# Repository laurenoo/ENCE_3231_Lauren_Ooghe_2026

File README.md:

# ENCE_3231_Lauren_Ooghe_2026
I did not complete this lab, but I tried using Timer 2 to create the 10us pulse. I used a prescalar of 83 and counter period of 9 to produce a 0.00001 s pulse. The block diagram was incomplete as well.

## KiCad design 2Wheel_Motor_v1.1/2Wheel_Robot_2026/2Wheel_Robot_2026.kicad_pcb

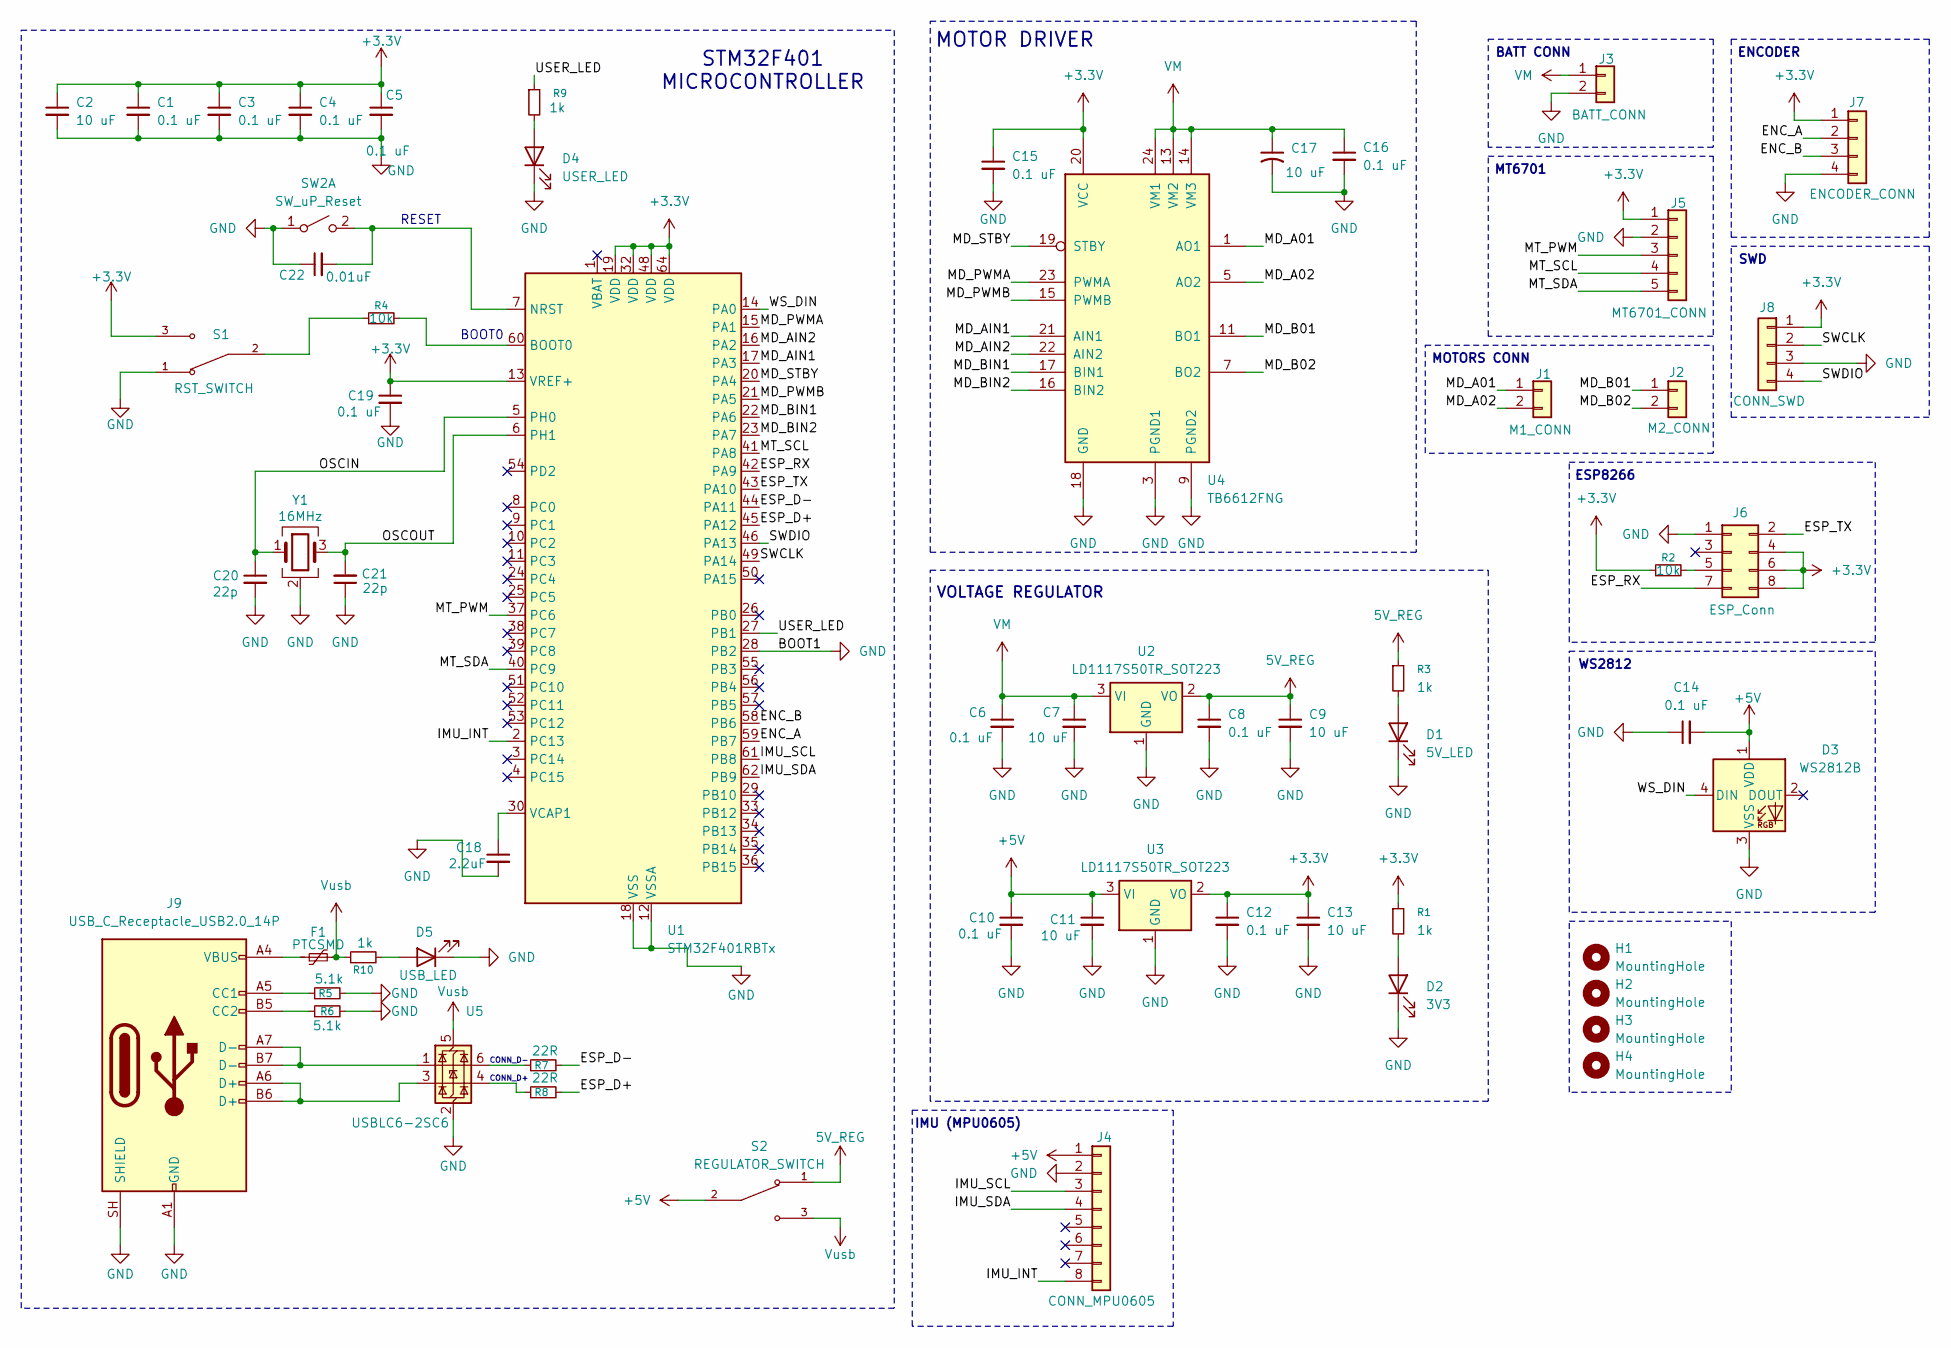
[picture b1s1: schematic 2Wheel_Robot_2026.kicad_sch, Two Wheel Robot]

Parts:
C1, C3, C4, C5, C6, C8, C10, C12, C14, C15, C16, C19: 0.1 uF; C_0805_2012Metric_Pad1.18x1.45mm_HandSolder; MFR# KAM21BR71H104JM
C2, C7, C9, C11, C13: 10 uF; C_0805_2012Metric_Pad1.18x1.45mm_HandSolder; MFR# KAM21BR71H104JM
C17: 10 uF; C_0805_2012Metric_Pad1.18x1.45mm_HandSolder
C18: 2.2uF; C_0805_2012Metric_Pad1.18x1.45mm_HandSolder; MFR# KAM21BR71H104JM
C20, C21: 22p; C_0805_2012Metric_Pad1.18x1.45mm_HandSolder; MFR# KAM21BR71H104JM
C22: 0.01uF; C_0805_2012Metric_Pad1.18x1.45mm_HandSolder; MFR# KAM21BR71H104JM
D1: 5V_LED; LED_0805_2012Metric_Pad1.15x1.40mm_HandSolder
D2: 3V3; LED_0805_2012Metric_Pad1.15x1.40mm_HandSolder
D3: WS2812B; LED_WS2812B_PLCC4_5.0x5.0mm_P3.2mm
D4: USER_LED; LED_0805_2012Metric_Pad1.15x1.40mm_HandSolder
D5: USB_LED; LED_0805_2012Metric_Pad1.15x1.40mm_HandSolder
F1: PTCSMD; Fuse_1812_4532Metric
H1, H2, H3, H4: MountingHole; MountingHole_2.2mm_M2
J1: M1_CONN; JST_XH_B2B-XH-A_1x02_P2.50mm_Vertical
J2: M2_CONN; JST_XH_B2B-XH-A_1x02_P2.50mm_Vertical
J3: BATT_CONN; JST_XH_B2B-XH-A_1x02_P2.50mm_Vertical
J4: CONN_MPU0605; PinSocket_1x08_P2.54mm_Vertical
J5: MT6701_CONN; JST_XH_B5B-XH-A_1x05_P2.50mm_Vertical
J6: ESP_Conn; PinSocket_2x04_P2.54mm_Vertical
J7: ENCODER_CONN; JST_XH_B4B-XH-A_1x04_P2.50mm_Vertical
J8: CONN_SWD; PinHeader_1x04_P2.54mm_Vertical
J9: USB_C_Receptacle_USB2.0_14P; USB_C_Receptacle_HCTL_HC-TYPE-C-16P-01A
R1, R3, R9, R10: 1k; R_0805_2012Metric_Pad1.20x1.40mm_HandSolder
R2, R4: 10k; R_0805_2012Metric_Pad1.20x1.40mm_HandSolder
R5, R6: 5.1k; R_0805_2012Metric_Pad1.20x1.40mm_HandSolder
R7, R8: 22R; R_0805_2012Metric_Pad1.20x1.40mm_HandSolder
S1: RST_SWITCH; SW_SLW-66527511-SMT-TR; PARTREV 1.01
S2: REGULATOR_SWITCH; SW_SLW-66527511-SMT-TR; PARTREV 1.01
SW2: SW_uP_Reset
U1: STM32F401RBTx; LQFP-64_10x10mm_P0.5mm; MFR# STM32F401RET6
U2, U3: LD1117S50TR_SOT223; SOT-223-3_TabPin2
U4: TB6612FNG; SSOP-24_5.3x8.2mm_P0.65mm
U5: USBLC6-2SC6; SOT-23-6
Y1: 16MHz; Crystal_SMD_Abracon_ABM8G-4Pin_3.2x2.5mm

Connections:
5V_REG: C8.1, C9.1, R3.1, S2.1, U2.2 (VO)
+3.3V: C1.1, C2.1, C3.1, C4.1, C5.1, C12.1, C13.1, C15.1, C19.1, J5.1, J6.4, J6.6, J6.8, J7.1, J8.1, R1.1, R2.1, S1.3, U1.13 (VREF+), U1.19 (VDD), U1.32 (VDD), U1.48 (VDD), U1.64 (VDD), U3.2 (VO), U4.20 (VCC)
+5V: C10.1, C11.1, C14.2, D3.1 (VDD), J4.1, S2.2, U3.3 (VI)
/ENC_A: J7.2, U1.59 (PB7)
/ENC_B: J7.3, U1.58 (PB6)
/ESP_D+: R8.2, U1.45 (PA12)
/ESP_D-: R7.2, U1.44 (PA11)
/ESP_RX: J6.7, U1.42 (PA9)
/ESP_TX: J6.2, U1.43 (PA10)
/IMU_INT: J4.8, U1.2 (PC13)
/IMU_SCL: J4.3, U1.61 (PB8)
/IMU_SDA: J4.4, U1.62 (PB9)
/MD_A01: J1.1, U4.1 (AO1), U4.2 (AO1)
/MD_A02: J1.2, U4.5 (AO2), U4.6 (AO2)
/MD_AIN1: U1.17 (PA3), U4.21 (AIN1)
/MD_AIN2: U1.16 (PA2), U4.22 (AIN2)
/MD_B01: J2.1, U4.11 (BO1), U4.12 (BO1)
/MD_B02: J2.2, U4.7 (BO2), U4.8 (BO2)
/MD_BIN1: U1.22 (PA6), U4.17 (BIN1)
/MD_BIN2: U1.23 (PA7), U4.16 (BIN2)
/MD_PWMA: U1.15 (PA1), U4.23 (PWMA)
/MD_PWMB: U1.21 (PA5), U4.15 (PWMB)
/MD_STBY: U1.20 (PA4), U4.19 (STBY)
/MT_PWM: J5.3, U1.37 (PC6)
/MT_SCL: J5.4, U1.41 (PA8)
/MT_SDA: J5.5, U1.40 (PC9)
/OSCIN: C20.1, U1.5 (PH0), Y1.1
/OSCOUT: C21.2, U1.6 (PH1), Y1.3
/SWCLK: J8.2, U1.49 (PA14)
/SWDIO: J8.4, U1.46 (PA13)
/USER_LED: R9.1, U1.27 (PB1)
/WS_DIN: D3.4 (DIN), U1.14 (PA0)
GND: C1.2, C2.2, C3.2, C4.2, C5.2, C6.2, C7.2, C8.2, C9.2, C10.2, C11.2, C12.2, C13.2, C14.1, C15.2, C16.2, C17.2, C18.2, C19.2, C20.2, C21.1, C22.1, D1.1 (K), D2.1 (K), D3.3 (VSS), D4.1 (K), D5.1 (K), J3.2, J4.2, J5.2, J6.1, J7.4, J8.3, J9.A1 (GND), J9.A12 (GND), J9.B1 (GND), J9.B12 (GND), J9.SH (SHIELD), R5.2, R6.2, S1.1, SW2.1 (A), U1.12 (VSSA), U1.18 (VSS), U1.28 (PB2), U1.31 (VSS), U1.47 (VSS), U1.63 (VSS), U2.1 (GND), U3.1 (GND), U4.3 (PGND1), U4.4 (PGND1), U4.9 (PGND2), U4.10 (PGND2), U4.18 (GND), U5.2 (GND), Y1.2 (G), Y1.4 (G)
unnamed: D1.2 (A), R3.2
unnamed: D2.2 (A), R1.2
unnamed: D4.2 (A), R9.2
unnamed: D5.2 (A), R10.2
unnamed: F1.1, J9.A4 (VBUS), J9.A9 (VBUS), J9.B4 (VBUS), J9.B9 (VBUS)
unnamed: J6.5, R2.2
unnamed: J9.A5 (CC1), R5.1
unnamed: J9.B5 (CC2), R6.1
unnamed: J9.A6 (D+), J9.B6 (D+), U5.3 (I/O2)
unnamed: J9.A7 (D-), J9.B7 (D-), U5.1 (I/O1)
unnamed: R4.1, S1.2
unnamed: R7.1, U5.6 (I/O1)
unnamed: R8.1, U5.4 (I/O2)
unnamed: C22.2, SW2.2 (B), U1.7 (NRST)
unnamed: R4.2, U1.60 (BOOT0)
unnamed: C18.1, U1.30 (VCAP1)
VM: C6.1, C7.1, C16.1, C17.1, J3.1, U2.3 (VI), U4.13 (VM2), U4.14 (VM3), U4.24 (VM1)
Vusb: F1.2, R10.1, S2.3, U5.5 (VBUS)

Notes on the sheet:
CONN_D-
MOTOR DRIVER
STM32F401 MICROCONTROLLER
VOLTAGE REGULATOR
MT6701
ENCODER
MOTORS CONN
BATT CONN
BOOT0
ESP8266
SWD
RESET
CONN_D+
IMU (MPU0605)
WS2812

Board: 2 copper layers, 60 parts (0 on the bottom side), 51 nets, no tracks yet.

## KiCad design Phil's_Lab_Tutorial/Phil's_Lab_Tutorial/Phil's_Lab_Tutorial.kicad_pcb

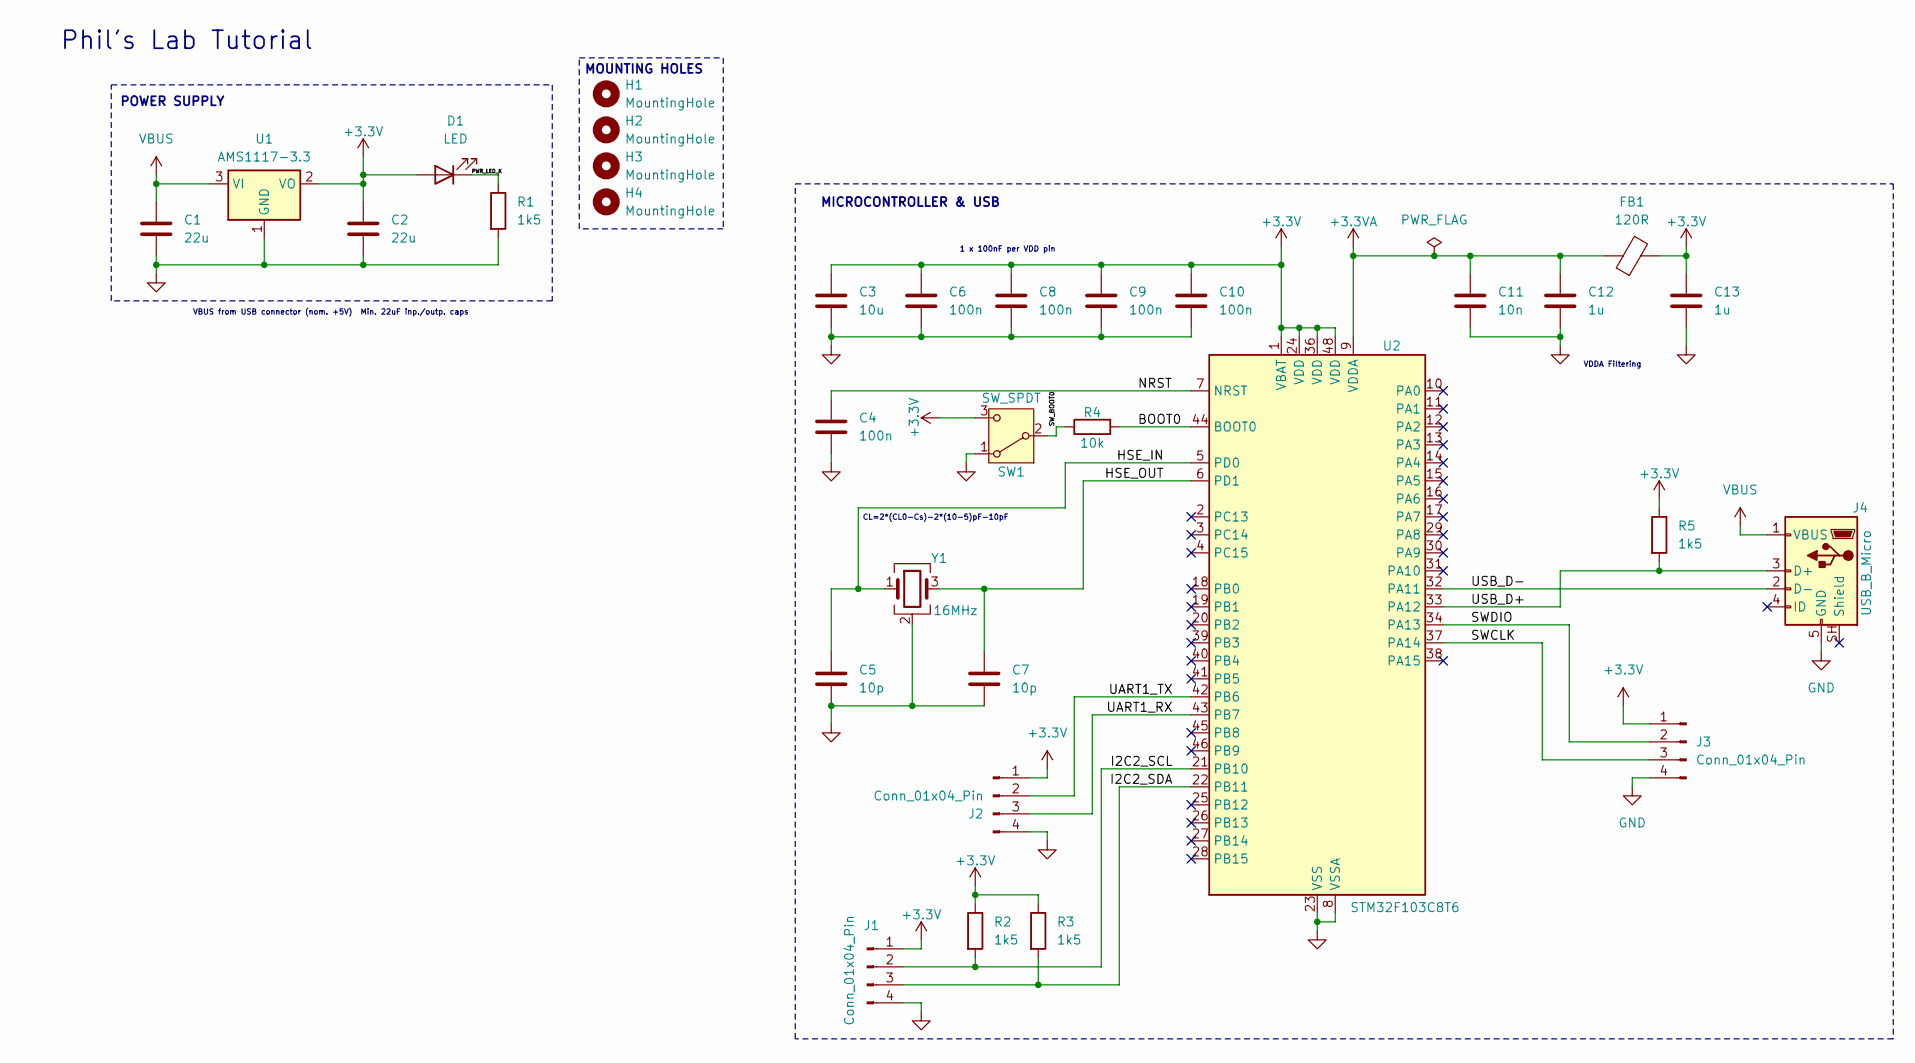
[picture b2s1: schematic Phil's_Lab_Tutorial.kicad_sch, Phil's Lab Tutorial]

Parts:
C1, C2: 22u; C_0805_2012Metric
C3: 10u; C_0603_1608Metric
C4, C6, C8, C9, C10: 100n; C_0402_1005Metric
C5, C7: 10p; C_0402_1005Metric
C11: 10n; C_0402_1005Metric
C12, C13: 1u; C_0402_1005Metric
D1: LED; LED_0805_2012Metric
FB1: 120R; L_0603_1608Metric
H1, H2, H3, H4: MountingHole; MountingHole_2.2mm_M2
J1, J2, J3: Conn_01x04_Pin; PinHeader_1x04_P2.54mm_Vertical
J4: USB_B_Micro; USB_Micro-B_Wuerth_629105150521
R1, R2, R3, R5: 1k5; R_0402_1005Metric
R4: 10k; R_0402_1005Metric
SW1: SW_SPDT; SW_SPDT_PCM12
U1: AMS1117-3.3; SOT-223-3_TabPin2
U2: STM32F103C8T6; LQFP-48_7x7mm_P0.5mm
Y1: 16MHz; Crystal_SMD_3225-4Pin_3.2x2.5mm

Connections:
+3.3V: C2.1, C3.1, C6.1, C8.1, C9.1, C10.1, C13.1, D1.2 (A), FB1.2, J1.1, J2.1, J3.1, R2.1, R3.1, R5.1, SW1.3 (C), U1.2 (VO), U2.1 (VBAT), U2.24 (VDD), U2.36 (VDD), U2.48 (VDD)
+3.3VA: C11.1, C12.1, FB1.1, U2.9 (VDDA)
/BOOT0: R4.2, U2.44 (BOOT0)
/HSE_IN: C5.1, U2.5 (PD0), Y1.1
/HSE_OUT: C7.1, U2.6 (PD1), Y1.3
/I2C2_SCL: J1.2, R2.2, U2.21 (PB10)
/I2C2_SDA: J1.3, R3.2, U2.22 (PB11)
/NRST: C4.1, U2.7 (NRST)
/PWR_LED_K: D1.1 (K), R1.1
/SWCLK: J3.3, U2.37 (PA14)
/SWDIO: J3.2, U2.34 (PA13)
/SW_BOOT0: R4.1, SW1.2 (B)
/UART1_RX: J2.3, U2.43 (PB7)
/UART1_TX: J2.2, U2.42 (PB6)
/USB_D+: J4.3 (D+), R5.2, U2.33 (PA12)
/USB_D-: J4.2 (D-), U2.32 (PA11)
GND: C1.2, C2.2, C3.2, C4.2, C5.2, C6.2, C7.2, C8.2, C9.2, C10.2, C11.2, C12.2, C13.2, J1.4, J2.4, J3.4, J4.5 (GND), R1.2, SW1.1 (A), U1.1 (GND), U2.8 (VSSA), U2.23 (VSS), U2.35 (VSS), U2.47 (VSS), Y1.2 (G), Y1.4 (G)
VBUS: C1.1, J4.1 (VBUS), U1.3 (VI)

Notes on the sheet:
VBUS from USB connector (nom. +5V) Min. 22uF inp./outp. caps
MICROCONTROLLER & USB
1 x 100nF per VDD pin
Phil's Lab Tutorial
MOUNTING HOLES
POWER SUPPLY
CL=2*(CL0-Cs)-2*(10-5)pF-10pF
VDDA Filtering

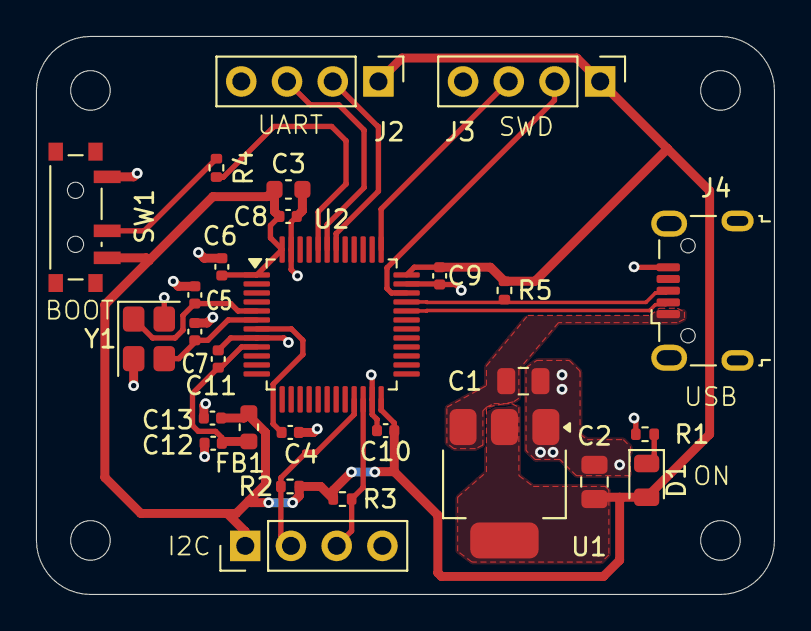
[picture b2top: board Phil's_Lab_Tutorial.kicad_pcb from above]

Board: 2 copper layers, 41.0 x 31.0 mm, 32 parts (0 on the bottom side), 18 nets.

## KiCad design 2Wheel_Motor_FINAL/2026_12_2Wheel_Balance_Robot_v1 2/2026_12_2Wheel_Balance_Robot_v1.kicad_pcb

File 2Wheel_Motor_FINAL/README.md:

# 2-Wheel Robot Design
## This project incorporates the use of program and design software such as STMCubeIDE and KiCad.
## Introduction
The main objective was to design and create a two-wheeled balancing robot using an STM32F401 microcontroller. All components were assembled to include soldering all components on the fabricated PCB, designing and cutting the acrylic chassis, and implementing test code for a 3-wheeled function to use for threshold testing.

### Block Diagram and System Diagram

 ### Design
 The PCB was designed in KiCAD and the images of layout and schematics can be seen below.

### Prototyping
Once all components were verified working, such as the ESP8266 wifi chip, the motors, and the USB connection, the chassis was designed using OnShape CAD program to provide a drawing that could be used to verify part placement such as the PCB, motor mounts, battery pack, and front caster wheel. 

Once the layout was verified with a 'dry fit', a .DXF file was downloaded from the CAD software and used in the laser cutter to shape and cut the acrylic chassis. All components were mounted and the robot was ready for testing.

### Testing
The 3-Wheel system is controlled by the use of an ESP8266 that provides a wifi signal (Access Point) to connect to a phone or tablet. The IP address is typed into the device and interfaces with the robot to perform manuevers such as forward, backward, left, right, or stop. The remote also receives a stream of data that is updated every 100 ms such as pitch, roll, velocity, and a counter. 

https://github.com/user-attachments/assets/3100aa6c-19b2-47c0-a776-326ca26b746c

Once the 3-wheeled task was completed, I was motivated to try to incorporate PID control to balance on two wheels. This introduced the encoder which was orignally to be an MT6701 but we were provided with an AS5600. The difference between these components is the address it uses to connect through I2C. I used Claude code to create a ".h" and ".c" file to include in the "main.c" program to initiate the encoder. Once this was accomplished, the code was written, tested, and verified. The testing consisted of finding the natural pitch recorded when the robot is balanced. This was used as the setpoint needed to determine whether the robot needs to correct forward or backward. Ultimately, the 2-wheel balanced was acheived but not perfected. 

https://github.com/user-attachments/assets/a37571b3-f4c5-43bc-a98e-a4f5ce808e1f

#### *** All PCB design materials and images are located in folder 2026_12_2Wheel_Balance_Robot_v1 2 ***
PCB layout used from Dr. Martins provided layout

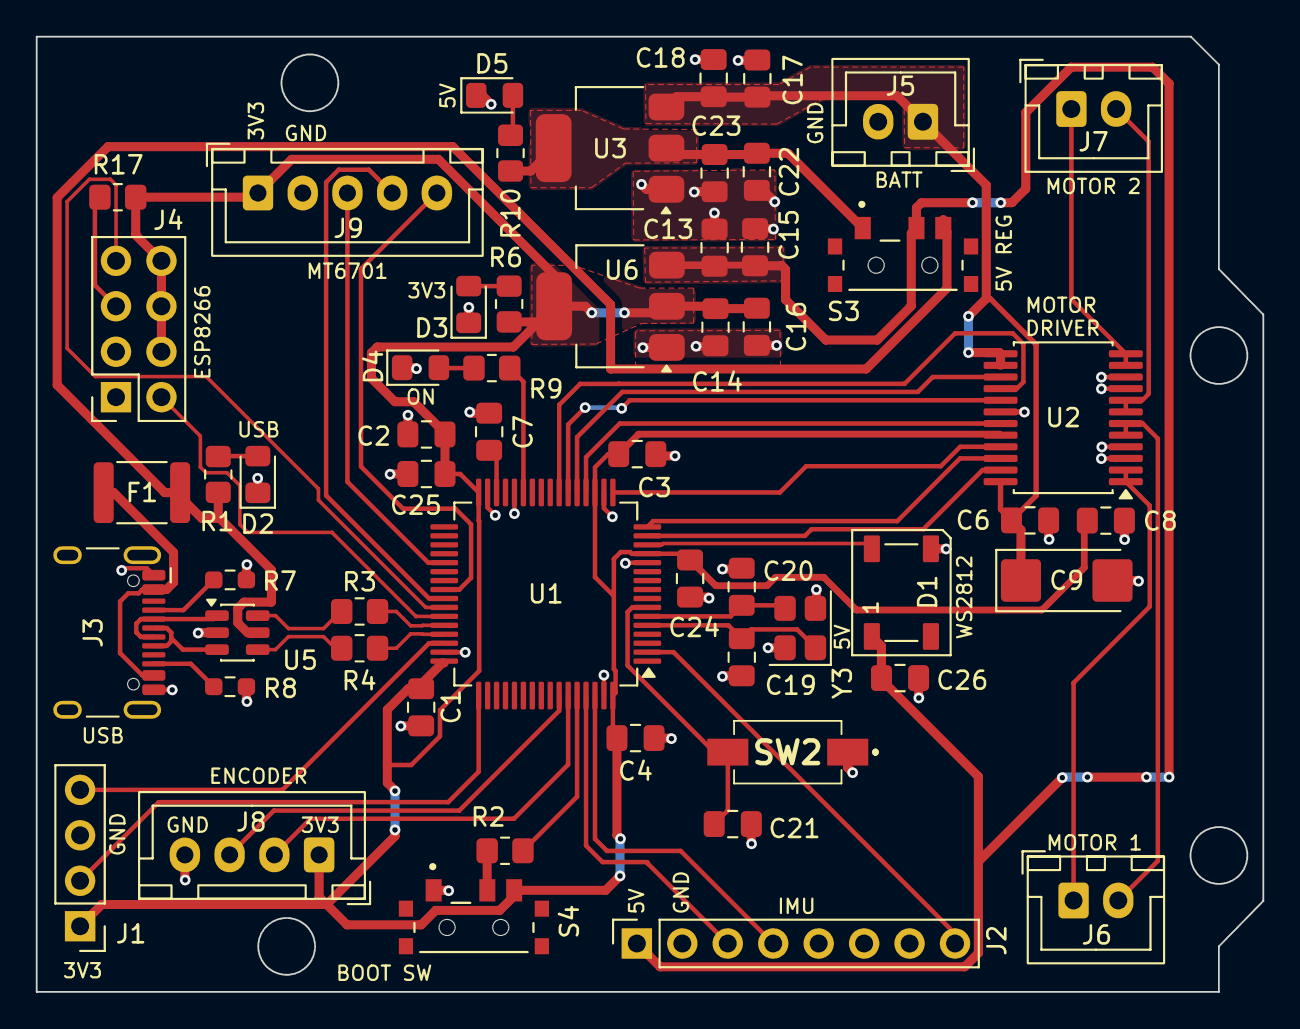
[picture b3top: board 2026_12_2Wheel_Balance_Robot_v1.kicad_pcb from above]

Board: 2 copper layers, 68.6 x 53.4 mm, 57 parts (1 on the bottom side), 51 nets.

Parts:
C1, C2, C3, C4, C6, C8, C13, C14, C17, C22, C24, C26: 0.1uF; C_0805_2012Metric_Pad1.18x1.45mm_HandSolder
C7: 2.2uF; C_0805_2012Metric_Pad1.18x1.45mm_HandSolder
C9: 10uF; CP_EIA-6032-28_Kemet-C_HandSolder
C15, C16, C18, C23, C25: 10uF; C_0805_2012Metric_Pad1.18x1.45mm_HandSolder
C19, C20: 22p; C_0805_2012Metric_Pad1.18x1.45mm_HandSolder
C21: 0.01uF; C_0805_2012Metric_Pad1.18x1.45mm_HandSolder
D1: WS2812B; LED_WS2812B_PLCC4_5.0x5.0mm_P3.2mm
D2: USB_LED; LED_0805_2012Metric_Pad1.15x1.40mm_HandSolder
D3: 3V3_LED; LED_0805_2012Metric_Pad1.15x1.40mm_HandSolder
D4: USER_LED; LED_0805_2012Metric_Pad1.15x1.40mm_HandSolder
D5: 5V_LED; LED_0805_2012Metric_Pad1.15x1.40mm_HandSolder
F1: PTCSMD; Fuse_1812_4532Metric
G: LOGO
J1: Conn_01x04; PinHeader_1x04_P2.54mm_Vertical
J2: CONN_MPU6050; PinSocket_1x08_P2.54mm_Vertical
J3: USB_C_Receptacle_USB2.0_14P; USB_C_Receptacle_HCTL_HC-TYPE-C-16P-01A
J4: ESP_Conn; PinSocket_2x04_P2.54mm_Vertical
J5: BATT_CONN; JST_XH_B2B-XH-A_1x02_P2.50mm_Vertical
J6: M1_CONN; JST_XH_B2B-XH-A_1x02_P2.50mm_Vertical
J7: M2_CONN; JST_XH_B2B-XH-A_1x02_P2.50mm_Vertical
J8: ENCODER_CONN; JST_XH_B4B-XH-A_1x04_P2.50mm_Vertical
J9: MT6701_CONN; JST_XH_B5B-XH-A_1x05_P2.50mm_Vertical
R1, R6, R9, R10: 1k; R_0805_2012Metric_Pad1.20x1.40mm_HandSolder
R2, R17: 10k; R_0805_2012Metric_Pad1.20x1.40mm_HandSolder
R3, R4: 22R; R_0805_2012Metric_Pad1.20x1.40mm_HandSolder
R7, R8: 5.1k; R_0603_1608Metric_Pad0.98x0.95mm_HandSolder
S3: REGULATOR_SWITCH; SW_SLW-66527511-SMT-TR
S4: RST_SWITCH; SW_SLW-66527511-SMT-TR
SW2: SW_uP_Reset
U1: STM32F401RBTx; LQFP-64_10x10mm_P0.5mm
U2: TB6612FNG; SSOP-24_5.3x8.2mm_P0.65mm
U3: LD1117S50TR_SOT223; SOT-223-3_TabPin2
U5: USBLC6-2SC6; SOT-23-6
U6: LD1117S33TR_SOT223; SOT-223-3_TabPin2
Y3: 16MHz; Crystal_SMD_Abracon_ABM8G-4Pin_3.2x2.5mm

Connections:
5V_REG: C22.1, C23.1, R10.2, S3.1, U3.2 (VO)
+3.3V: C1.1, C2.1, C3.1, C4.1, C8.1, C14.1, C16.1, C24.1, C25.1, J1.1, J4.4, J4.6, J4.8, J8.1, J9.1, R6.2, R17.1, S4.3, U1.13 (VREF+), U1.19 (VDD), U1.32 (VDD), U1.48 (VDD), U1.64 (VDD), U2.20 (VCC), U6.2 (VO)
+5V: C13.1, C15.1, C26.2, D1.1 (VDD), J2.1, S3.2, U6.3 (VI)
/BOOT0: R2.2, U1.60 (BOOT0)
/CONN_D+: R4.1, U5.4 (I/O2)
/CONN_D-: R3.1, U5.6 (I/O1)
/ENC_A: J8.2, U1.59 (PB7)
/ENC_B: J8.3, U1.58 (PB6)
/ESD_D+: R4.2, U1.45 (USB_OTG_FS_DP)
/ESD_D-: R3.2, U1.44 (USB_OTG_FS_DM)
/ESP_RX: J4.7, U1.42 (USART1_TX)
/ESP_TX: J4.2, U1.43 (USART1_RX)
/IMU_INT: J2.8, U1.2 (PC13)
/IMU_SCL: J2.3, U1.61 (I2C1_SCL)
/IMU_SDA: J2.4, U1.62 (I2C1_SDA)
/MD_AIN1: U1.17 (PA3), U2.21 (AIN1)
/MD_AIN2: U1.16 (PA2), U2.22 (AIN2)
/MD_AO1: J6.1, U2.1 (AO1), U2.2 (AO1)
/MD_AO2: J6.2, U2.5 (AO2), U2.6 (AO2)
/MD_BIN1: U1.22 (PA6), U2.17 (BIN1)
/MD_BIN2: U1.23 (PA7), U2.16 (BIN2)
/MD_BO1: J7.1, U2.11 (BO1), U2.12 (BO1)
/MD_BO2: J7.2, U2.7 (BO2), U2.8 (BO2)
/MD_PWMA: U1.15 (TIM2_CH2), U2.23 (PWMA)
/MD_PWMB: U1.21 (TIM2_CH1), U2.15 (PWMB)
/MD_STBY: U1.20 (PA4), U2.19 (STBY)
/MT_PWM: J9.3, U1.37 (PC6)
/MT_SCL: J9.4, U1.41 (I2C3_SCL)
/MT_SDA: J9.5, U1.40 (I2C3_SDA)
/OSCIN: C19.2, U1.5 (RCC_OSC_IN), Y3.1
/OSCOUT: C20.2, U1.6 (RCC_OSC_OUT), Y3.3
/RESET: C21.1, SW2.2 (B), U1.7 (NRST)
/SWCLK: J1.2, U1.49 (SYS_JTCK-SWCLK)
/SWDIO: J1.4, U1.46 (SYS_JTMS-SWDIO)
/USB_D+: J3.A6 (D+), J3.B6 (D+), U5.3 (I/O2)
/USB_D-: J3.A7 (D-), J3.B7 (D-), U5.1 (I/O1)
/USER_LED: R9.2, U1.27 (PB1)
/WS_DIN: D1.4 (DIN), U1.14 (TIM5_CH1)
GND: C1.2, C2.2, C3.2, C4.2, C6.2, C7.2, C8.2, C9.2, C13.2, C14.2, C15.2, C16.2, C17.2, C18.2, C19.1, C20.1, C21.2, C22.2, C23.2, C24.2, C25.2, C26.1, D1.3 (VSS), D2.1 (K), D3.1 (K), D4.1 (K), D5.1 (K), J1.3, J2.2, J3.A1 (GND), J3.A12 (GND), J3.B1 (GND), J3.B12 (GND), J3.SH (SHIELD), J4.1, J5.2, J8.4, J9.2, R7.1, R8.2, S4.1, SW2.1 (A), U1.12 (VSSA), U1.18 (VSS), U1.28 (PB2), U1.31 (VSS), U1.47 (VSS), U1.63 (VSS), U2.3 (PGND1), U2.4 (PGND1), U2.9 (PGND2), U2.10 (PGND2), U2.18 (GND), U3.1 (GND), U5.2 (GND), U6.1 (GND), Y3.2, Y3.4
unnamed: D2.2 (A), R1.1
unnamed: D3.2 (A), R6.1
unnamed: D4.2 (A), R9.1
unnamed: D5.2 (A), R10.1
unnamed: F1.1, J3.A4 (VBUS), J3.A9 (VBUS), J3.B4 (VBUS), J3.B9 (VBUS)
unnamed: J3.A5 (CC1), R7.2
unnamed: J3.B5 (CC2), R8.1
unnamed: J4.5, R17.2
unnamed: R2.1, S4.2
unnamed: C7.1, U1.30 (VCAP1)
VM: C6.1, C9.1, C17.1, C18.1, J5.1, U2.13 (VM2), U2.14 (VM3), U2.24 (VM1), U3.3 (VI)
Vusb: F1.2, R1.2, S3.3, U5.5 (VBUS)

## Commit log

2026-04-16 Update README with lab completion status and details
    Added a note about incomplete lab work and Timer 2 usage.
2026-04-17 Rename Block diagram.png to LAB_1/Block diagram.png
2026-04-17 Rename Embedded Systems.png to LAB_1/Embedded Systems.png
2026-04-17 Update README with lab progress and Timer usage
    Added detailed notes on Timer 1 and Timer 2 usage for Ultrasonic Sensor pulse generation and echo capture.
2026-04-17 Rename Project_HC_SR04.zip to UPDATED_Project_HC_SR04.zip
2026-06-08 Refactor README for improved readability
    Removed unnecessary header formatting for clarity.
2026-06-09 Enhance README with diagrams and project details
    Added images and additional sections for block and system diagrams.
2026-06-09 Revise section titles in README.md
    Updated section titles and improved clarity in the README.
2026-06-09 Update README with new image and project details
    Added an additional image and improved project description.
2026-06-09 Fix spelling and update image dimensions in README
    Updated image dimensions and corrected spelling errors in the project description.
2026-06-09 Fix image dimensions in README.md
    Correct the image width and height attributes in README.
2026-06-09 Fix README.md spelling and update image size
    Corrected image dimensions and fixed spelling errors in the project description.
2026-06-09 Adjust image dimensions in README.md
    Updated image size for better display.
2026-06-09 Update images and fix typo in README
    Replaced an image in the README and corrected a typo.
2026-06-09 Fix typos and enhance README clarity
    Corrected typos and improved sentence structure in the README.
2026-06-09 Fix spelling and enhance project description in README
    Corrected spelling errors and added details about the 3-wheel system's control and data streaming.
2026-06-09 Revise README for clarity and detail
    Updated the README to correct wording and enhance clarity regarding the project objectives and components used.
2026-06-09 Refactor README for improved structure and clarity
    Reorganized README content to separate sections for clarity, adding a new 'Testing' section and refining existing descriptions.
2026-06-09 Update README with 2-wheel system details and testing
    Added details about the transition from a 3-wheel to a 2-wheel system, including the use of PID control and encoder specifications.
2026-06-09 Rename 2Wheel_Motor_FINAL/2026_STM32F401_3Wheel_Balance.zip to 2Wheel_Motor_FINAL/STMCubeIDE_Code/2026_STM32F401_3Wheel_Balance.zip
2026-06-09 Clarify .DXF file usage and robot testing readiness
    Updated the README to clarify the process of downloading the .DXF file and added details about the robot's readiness for testing after component mounting.
